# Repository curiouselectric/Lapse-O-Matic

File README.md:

# Solar Powered ESP32 Camera For Wildlife and Time-Lapse
This is code, PCB and enclosure design for an ESP32_CAM based, solar powered wildlife camera

This unit is based on the ESP32_CAM.

Code has been written to upload onto the ESP32.

Control of the unit is through a "settings.txt" file on the SD card.

The unit can either be in "LAPSE" mode (where it wakes up every set period and takes a photo/number of photos) or it can be in "TRIGGER" mode where it will take a number of photos when the unit is triggered. It will then go back to sleep.

Triggering can either be done with a PIR, or with an external switch.

This unit has an input for a small solar panel to recharge an 18650 Li Ion cell, so it can be left for remote monitoring.

A flash can be implemented, with a start and stop delay to adjust shadow effects.

This code relies heaviliy on the following tutorials and information:

* https://techtutorialsx.com/2020/06/27/esp32-connecting-to-sd-card/
* https://randomnerdtutorials.com/esp32-cam-take-photo-save-microsd-card/
* https://www.olimex.com/Products/IoT/ESP32/ESP32-CAM/
* https://marksbench.com/electronics/esp32-cam-low-power-trail-camera/
* https://hackaday.com/2020/05/18/esp32-trail-camera-goes-the-distance-on-aa-batteries/
* https://randomnerdtutorials.com/esp32-cam-ai-thinker-pinout/
* https://dronebotworkshop.com/esp32-cam-intro/

## ESP32 Code

Please follow these instructions for setting up your arduino IDE to upload code to the ESP32_CAM.

There is no USB connection to the ESP32_CAM, so I used this nice programmer from Tindie (around £10 UK):
https://www.tindie.com/products/bitluni/cam-prog/

The code starts by reading the settings.txt file on the root directoy of the SD card. If the SD card fails to mount, then the unit will go to default settings, which will mean sleeping for 10 seconds then trying the SD card again.
If there is no settings.txt file then the unit will use the default values (stored in the config.h page of the firmware).

## Settings file

Here is an example settings.txt file:

    // Adjust these settings as required: //
    FLASH_FLAG=1
    NUMBER_PHOTOS=4
    TIME_TO_SLEEP=800
    MODE=TRIGGER
    PHOTO_DELAY=250
    FLASH_START_DELAY=100
    FLASH_STOP_DELAY=100
    DEBUG_FLAG=1
    DEBUG_PHOTO=1
    // END OF SETTINGS - LEAVE THIS LINE  //

* FLASH_FLAG - Use a flash with the photo? (0 (OFF) or 1 (ON))
* NUMBER_PHOTOS - How many photos to take when waking up?
* TIME_TO_SLEEP - How long (in seconds) between wake-ups (when in SLEEP mode)
* MODE - The mode to use is either LAPSE (wake up every TIME_TO_SLEEP seconds) or TRIGGER (either wake up on PIR trigger or external trigger)
* PHOTO_DELAY - delay (in milli Seconds) between taking the photos.
* FLASH_START_DELAY - Flash will switch on then wait this time before taking photo (in milli Seconds)
* FLASH_STOP_DELAY - Flash will be on and wait this time after taking photo (in milli Seconds)
* DEBUG_FLAG - See debug info on serial port (0 (OFF) or 1 (ON))
* DEBUG_PHOTO - See debug info on serial port (0 (OFF) or 1 (ON))

*Note: Spaces can be used in the WIFI SSID. Do not use spaces around the equals sign.*

## Solar Power

This unit has a sinlge 18650 lithium polymer cell for power. This has a battery charging circuit using one cell PV module.

Based upon the BQ24210 800mA, single-input, single cell Li-ion Solar battery charger from Texas Instruments:

https://www.ti.com/sitesearch/docs/universalsearch.tsp?searchTerm=BQ24210#q=BQ24210&t=everything&linkId=1

## PCB design

PCB is designed in KiCAD.

A Real Time Clock (RTC) has been added to use as a timestamp on the photo files. This can also be used for the timing of the unit wake up.

## WiFi Upload

This unit uses ReadyMail from mobizt to send photos via an email SMTP server to any email address. You must set up your own email from which to send photos (I used gmail).

This is not always totally reliable, especially if any reception issues. But photos are still saved on the SD card.

## More information

There is lots more about this project at this blog post:

[*https://www.curiouselectric.co.uk/blogs/blog/prototyping-a-wildlife-camera**](https://www.curiouselectric.co.uk/blogs/blog/prototyping-a-wildlife-camera)

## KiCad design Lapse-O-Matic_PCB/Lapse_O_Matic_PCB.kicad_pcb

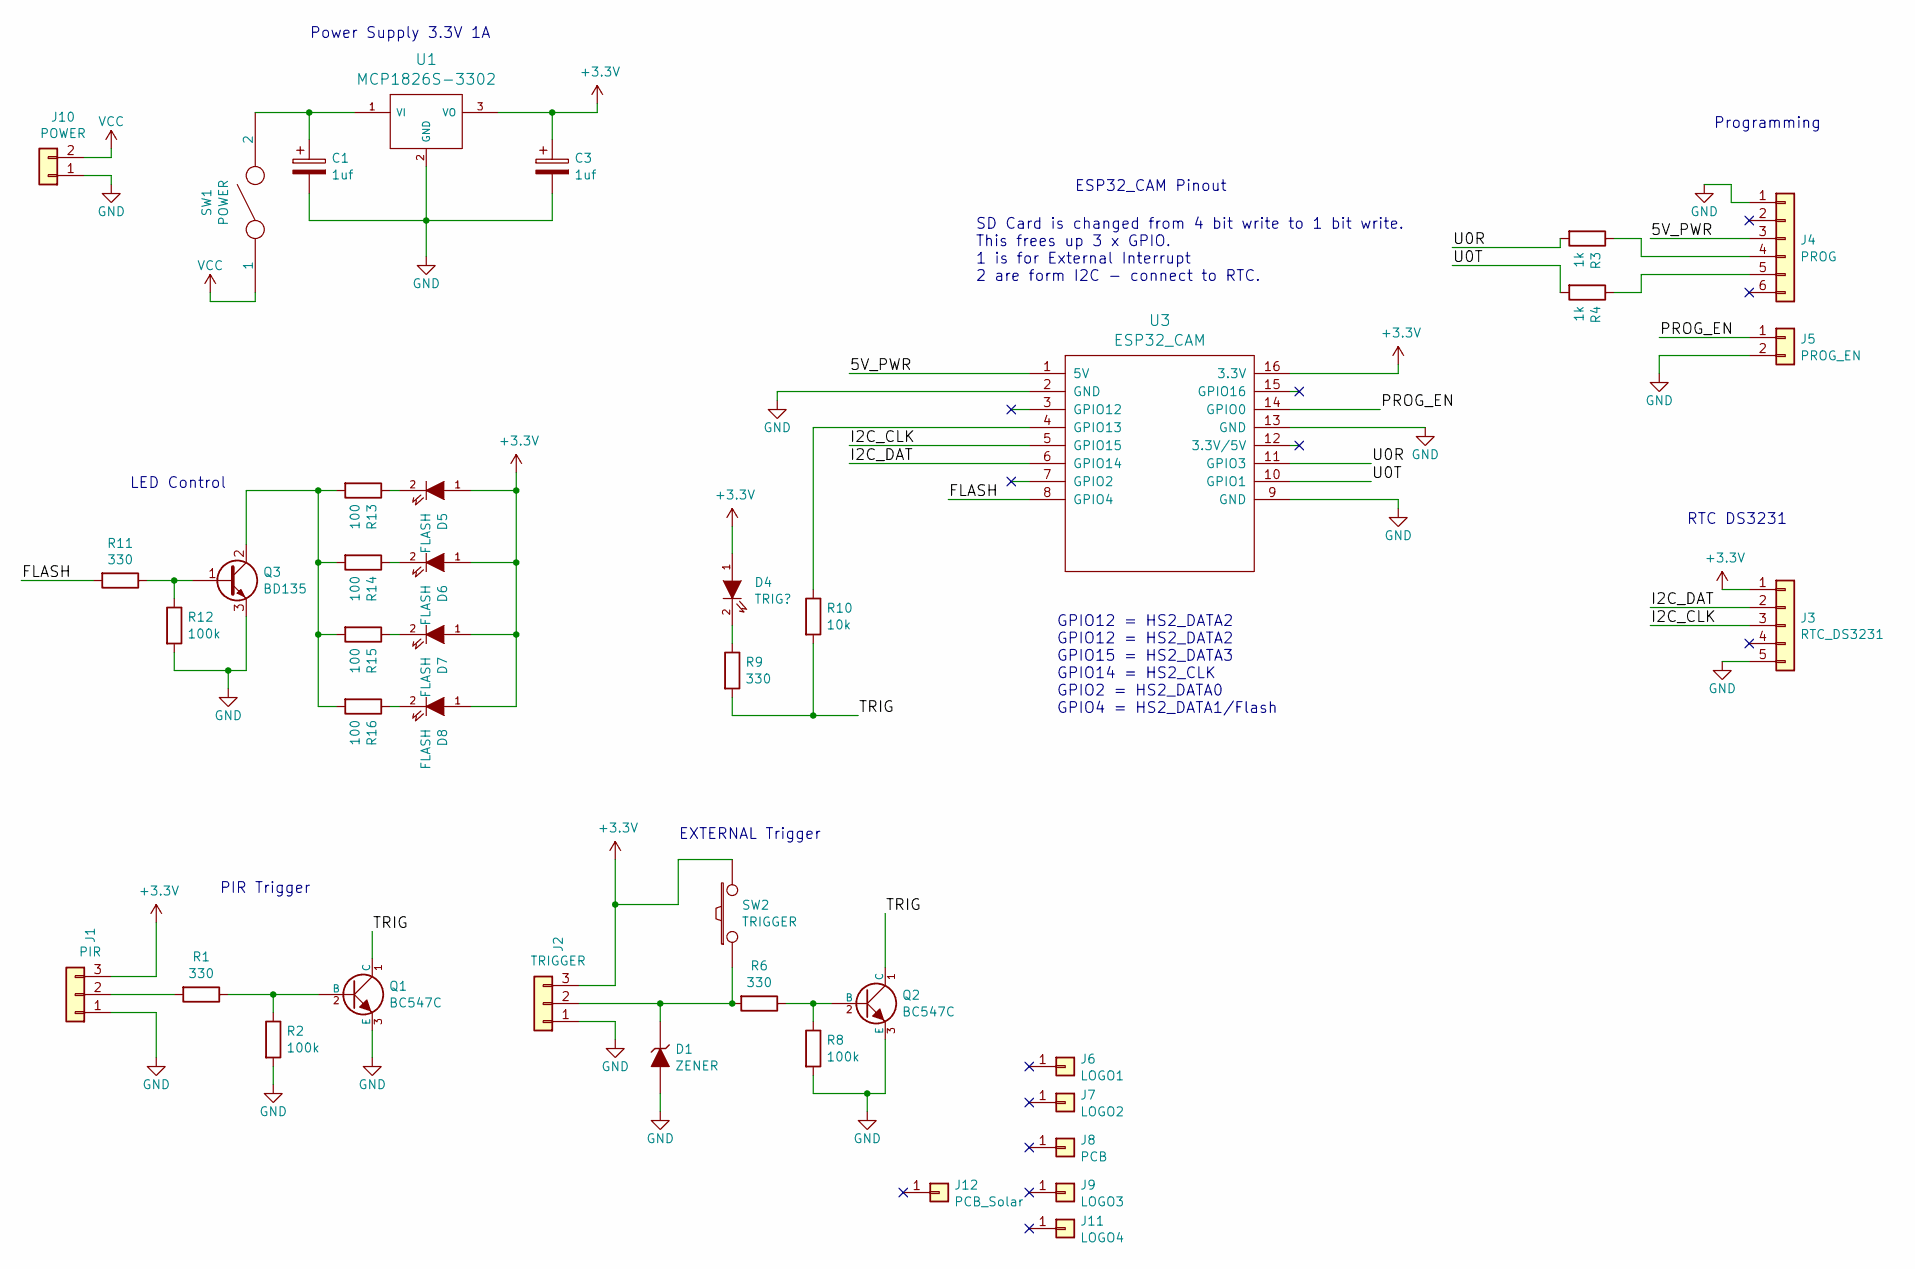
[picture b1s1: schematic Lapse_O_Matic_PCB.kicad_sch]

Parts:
C1, C3: 1uf; C_1V7_TH
D1: ZENER; TH_Diode_3
D4: TRIG?; TH_LED-5MM
D5, D6, D7, D8: FLASH; TH_LED-5MM
J1: PIR; SIL-3_PIR_SENSOR
J2: TRIGGER; SIL-3_screw_terminal
J3: RTC_DS3231; TH_RTC_MODULE_SM
J4: PROG; TH_6x1_CONN
J5: PROG_EN; TH_Pin_Header_Straight_1x02
J6: LOGO1; TCEC_Words_13mm
J7: LOGO2; 2019_011_16_CuriousElectricCompany_Logo_Round_Logo_No_words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
J8: PCB; PCB_Lapse-O-Matic
J9: LOGO3; lapseomatic logo_20x6mm
J10: POWER; SIL-2_screw_terminal
J11: LOGO4; lapseomatic logo_20x6mm
J12: PCB_Solar
Q1, Q2: BC547C; NPN_BC337
Q3: BD135; TO220_BD135
R1, R6, R9, R11: 330; TH_Resistor_1
R2, R8, R12: 100k; TH_Resistor_1
R3, R4: 1k; TH_Resistor_1
R10: 10k; TH_Resistor_1
R13, R14, R15, R16: 100; TH_Resistor_1
SW1: POWER; SW_SPDT_R_Angle_ALIEX
SW2: TRIGGER; SW_PUSH_SMALL_lg_pad
U1: MCP1826S-3302; TO220_MCP1826S
U3: ESP32_CAM

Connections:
+3V3: C3.1, D4.1 (A), D5.1 (A), D6.1 (A), D7.1 (A), D8.1 (A), J1.3, J2.3, J3.1, SW2.2, U1.3 (VO), U3.16 (3.3V)
/5V_PWR: J4.3, U3.1 (5V)
/FLASH: R11.2, U3.8 (GPIO4)
/I2C_CLK: J3.3, U3.5 (GPIO15)
/I2C_DAT: J3.2, U3.6 (GPIO14)
/PROG_EN: J5.1, U3.14 (GPIO0)
/TRIG: Q1.1 (C), Q2.1 (C), R9.2, R10.2
/U0R: R3.2, U3.11 (GPIO3)
/U0T: R4.2, U3.10 (GPIO1)
GND: C1.2, C3.2, D1.2 (A), J1.1, J2.1, J3.5, J4.1, J5.2, J10.1, Q1.3 (E), Q2.3 (E), Q3.3 (E), R2.2, R8.2, R12.2, U1.2 (GND), U3.2 (GND), U3.9 (GND), U3.13 (GND)
unnamed: C1.1, SW1.2, U1.1 (VI)
unnamed: D1.1 (K), J2.2, R6.2, SW2.1
unnamed: D4.2 (K), R9.1
unnamed: D5.2 (K), R13.1
unnamed: D6.2 (K), R14.1
unnamed: D7.2 (K), R15.1
unnamed: D8.2 (K), R16.1
unnamed: J1.2, R1.2
unnamed: J4.4, R3.1
unnamed: J4.5, R4.1
unnamed: Q1.2 (B), R1.1, R2.1
unnamed: Q2.2 (B), R6.1, R8.1
unnamed: Q3.1 (B), R11.1, R12.1
unnamed: Q3.2 (C), R13.2, R14.2, R15.2, R16.2
unnamed: R10.1, U3.4 (GPIO13)
VCC: J10.2, SW1.1

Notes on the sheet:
LED Control
RTC DS3231
Programming
ESP32_CAM Pinout
PIR Trigger
Power Supply 3.3V 1A
SD Card is changed from 4 bit write to 1 bit write. This frees up 3 x GPIO. 1 is for External Interrupt 2 are form I2C - connect to RTC.
EXTERNAL Trigger
GPIO12 = HS2_DATA2 GPIO12 = HS2_DATA2 GPIO15 = HS2_DATA3 GPIO14 = HS2_CLK GPIO2 = HS2_DATA0 GPIO4 = HS2_DATA1/Flash

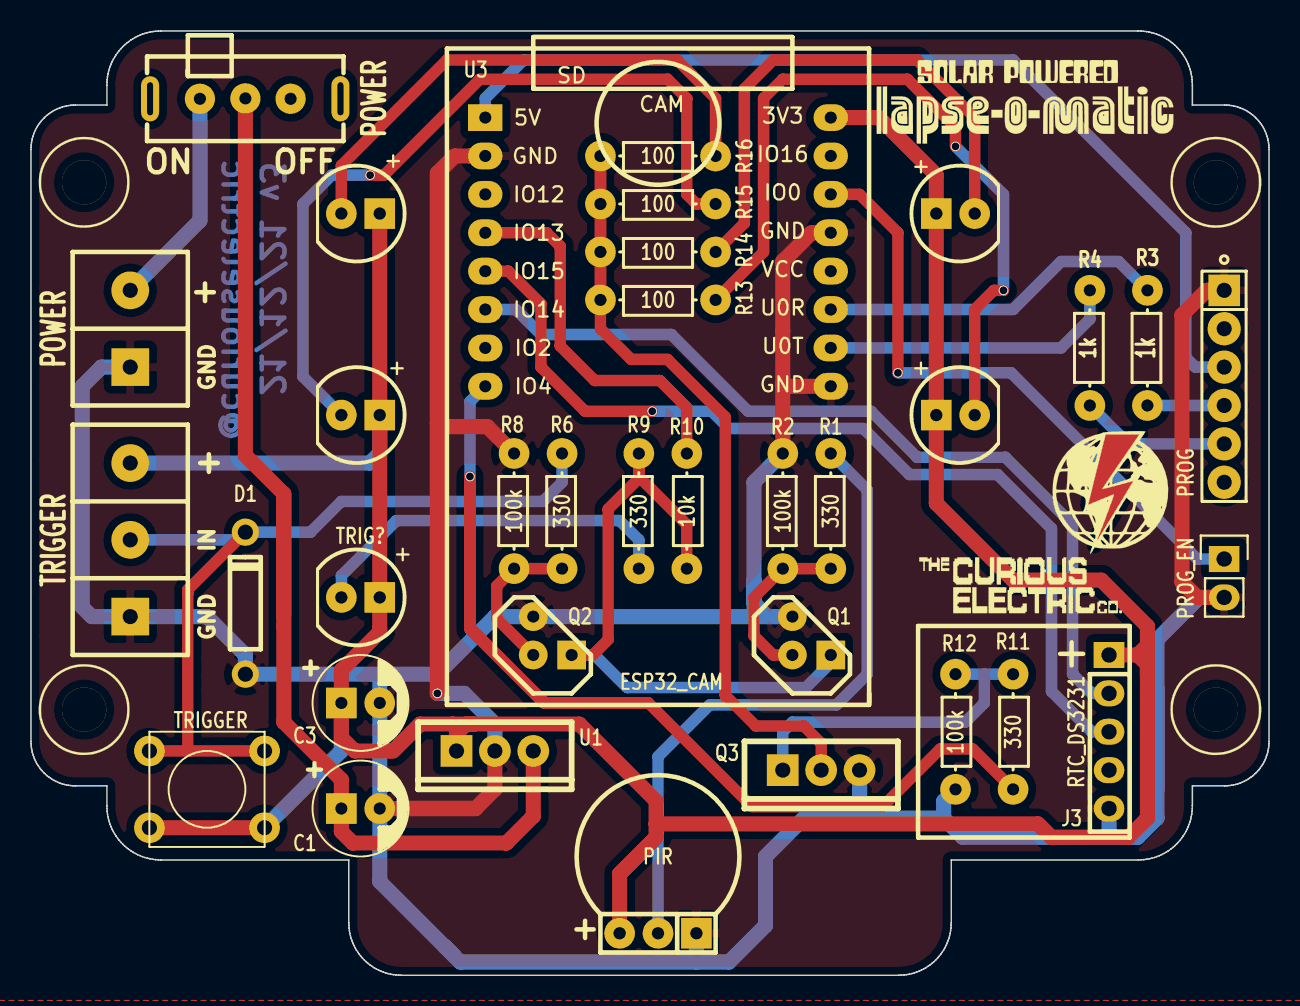
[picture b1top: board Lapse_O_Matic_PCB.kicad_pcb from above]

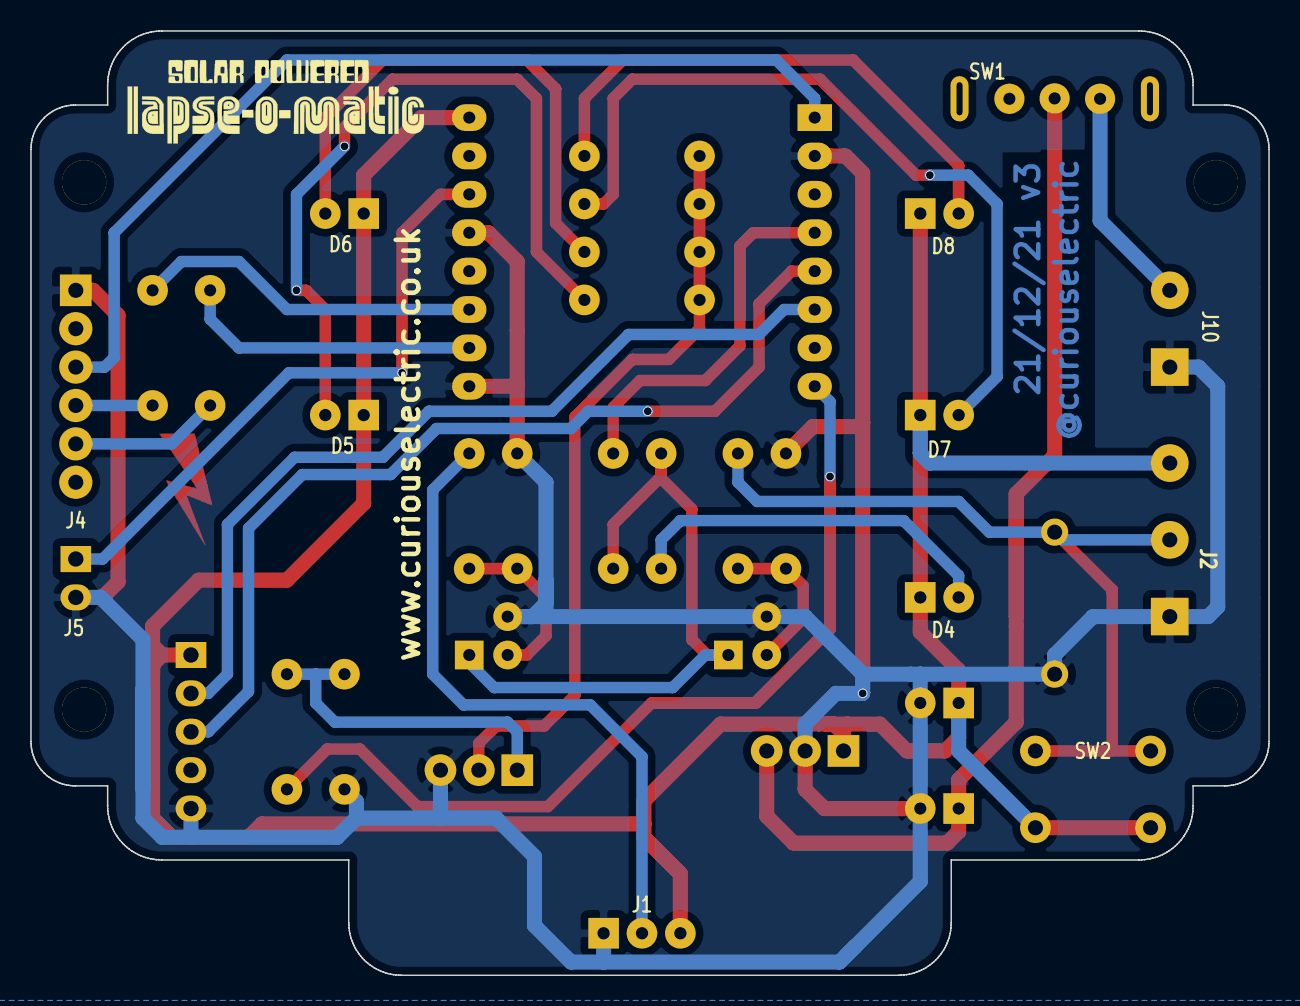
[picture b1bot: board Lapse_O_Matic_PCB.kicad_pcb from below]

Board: 2 copper layers, 81.9 x 62.5 mm, 40 parts (3 on the bottom side), 26 nets.

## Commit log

2020-08-31 Initial comit of PCB and Firmware
2020-08-31 Updated Settings and readme
2020-08-31 Updated Schematic
2020-09-01 Updated with RTC for filename
2020-09-01 Update WildlifeCamera.ino
    Got RTC working
2020-09-02 PCB update
    Sorted most footprints. Put Items in correct places. Not yet routed
2020-09-04 Updated firmware with SD error logging
2020-11-21 Update of PCB
2020-12-05 Update of code - sorting libraries
2020-12-18 Large update with email sending code
2020-12-18 Moved RTC tests
2021-07-19 Added new PCB design
    Add on for solar charger module. Lapse-O-Matic
2021-07-20 Small updates to PCB
2021-08-12 PCB updates
    Updated PCB
2021-12-17 Re-name
2021-12-17 Cleaned up
2021-12-20 Updated with new ESP Mail Client
2021-12-22 updated PCB and hardware
2022-01-18 Big update of PCB and Code
2022-01-18 small code update
2022-01-28 updated code and hardware
    sorted issues with PIR trigger - electrical noise from wifi. Stop wifi. wait then sleep. no retrigger!
2022-02-03 Updated hardware and firmware
    Better code for PIR enable
    Redesigned whole baseplate design
2022-02-03 updated baseplate files
2025-07-07 Large update of code to Jul 2025
